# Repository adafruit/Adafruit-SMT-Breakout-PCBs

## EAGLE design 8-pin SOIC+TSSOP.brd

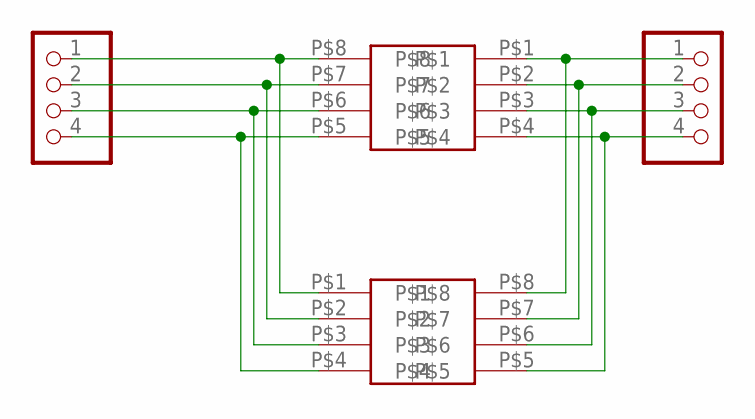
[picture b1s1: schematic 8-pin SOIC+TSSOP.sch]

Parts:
CN1, CN2: PADS-4
U$1: 8-PINSOIC-NW; SO8NW
U$2: 8-PINTSSOP; TSSOP8

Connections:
unnamed: CN1.1, U$1.P$8, U$2.P$1
unnamed: CN2.1, U$1.P$1, U$2.P$8
unnamed: CN2.2, U$1.P$2, U$2.P$7
unnamed: CN2.3, U$1.P$3, U$2.P$6
unnamed: CN2.4, U$1.P$4, U$2.P$5
unnamed: CN1.2, U$1.P$7, U$2.P$2
unnamed: CN1.3, U$1.P$6, U$2.P$3
unnamed: CN1.4, U$1.P$5, U$2.P$4

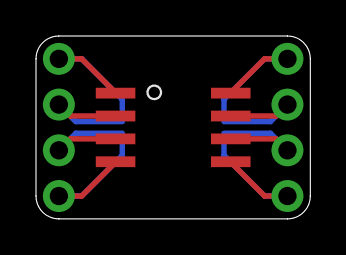
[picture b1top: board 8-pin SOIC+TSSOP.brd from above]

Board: 2 copper layers, 15.2 x 10.2 mm, 4 parts (1 on the bottom side), 8 nets.

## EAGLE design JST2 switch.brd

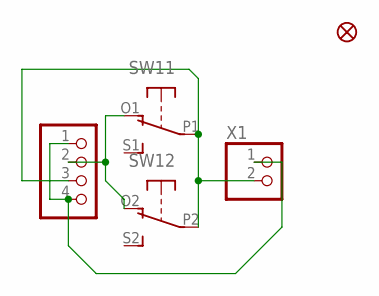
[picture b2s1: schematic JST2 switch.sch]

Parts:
FID1: FIDUCIAL""; FIDUCIAL_1MM
JP1: PADS-4
SW1: DPDT-EG1390; EG1390
X1: CON_JST_PH_2PIN; JSTPH2

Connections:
GND: JP1.1, JP1.4, X1.1
unnamed: JP1.3, SW1.P1, SW1.P2, X1.2
unnamed: JP1.2, SW1.O1 (O), SW1.O2 (O)

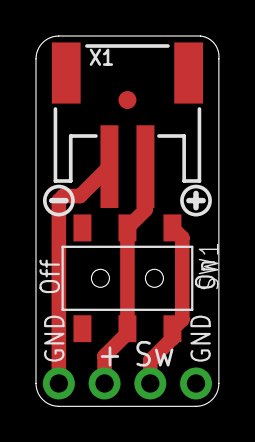
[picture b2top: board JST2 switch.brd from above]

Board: 2 copper layers, 10.2 x 20.6 mm, 7 parts (1 on the bottom side), 3 nets.

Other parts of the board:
U$1: SYMBOL_PLUS
U$2: SYMBOL_MINUS
U$3: ADAFRUIT_5MM

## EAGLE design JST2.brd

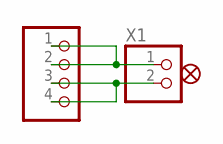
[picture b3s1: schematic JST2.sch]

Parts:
FID1: FIDUCIAL""; FIDUCIAL_1MM
JP1: PADS-4
X1: CON_JST_PH_2PIN; JSTPH2

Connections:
unnamed: JP1.1, JP1.2, X1.1
unnamed: JP1.3, JP1.4, X1.2

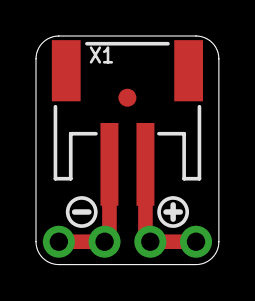
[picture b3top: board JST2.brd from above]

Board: 2 copper layers, 10.2 x 12.7 mm, 6 parts (1 on the bottom side), 2 nets.

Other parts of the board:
U$1: SYMBOL_PLUS
U$2: SYMBOL_MINUS
U$4: ADAFRUIT_3.5MM

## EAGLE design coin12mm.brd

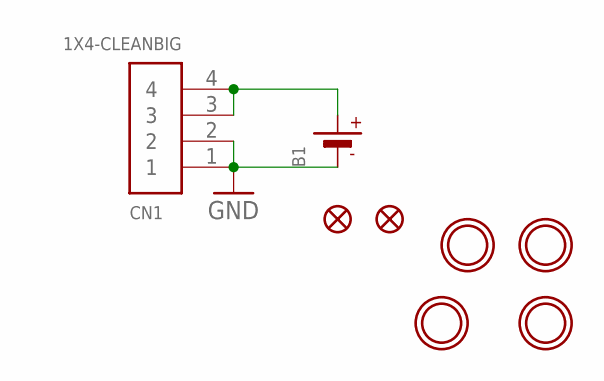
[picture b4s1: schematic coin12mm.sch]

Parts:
B1: BATTERYCR1220_SMT; CR1220
CN1: 1X4-CLEANBIG; 1X04-CLEANBIG
FID1, FID2: FIDUCIAL""; FIDUCIAL_1MM
U$1, U$2, U$3, U$5: MOUNTINGHOLE2.5; MOUNTINGHOLE_2.5_PLATED

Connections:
GND: B1.-, CN1.1, CN1.2
unnamed: B1.+$1 (+), CN1.3, CN1.4

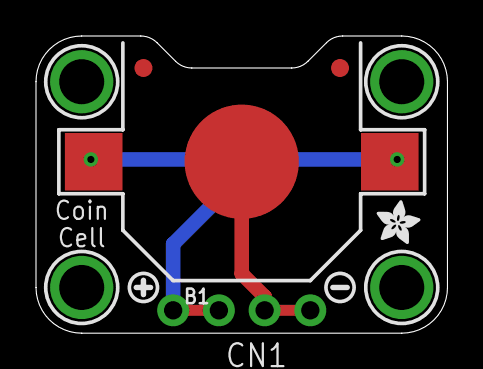
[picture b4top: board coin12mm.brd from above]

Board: 2 copper layers, 22.9 x 16.5 mm, 12 parts (1 on the bottom side), 2 nets.

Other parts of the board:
U$4: ADAFRUIT_5MM
U$6: SYMBOL_PLUS
U$7: SYMBOL_MINUS
U$8: ADAFRUIT_2.5MM

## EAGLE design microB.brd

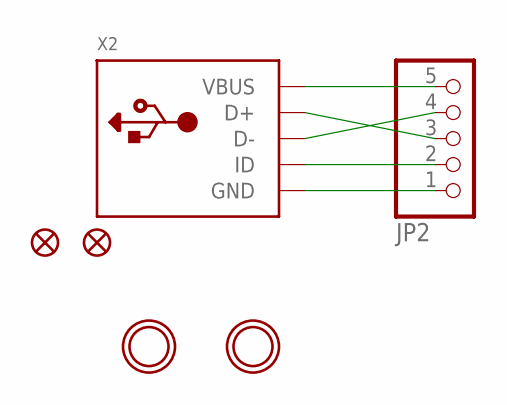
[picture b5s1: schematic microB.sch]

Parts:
FID1, FID2: FIDUCIAL""; FIDUCIAL_1MM
JP2: HEADER-1X570MIL; 1X05_ROUND_70
U$1, U$2: MOUNTINGHOLE2.5; MOUNTINGHOLE_2.5_PLATED
X2: USBMICRO_20329; 4UCONN_20329

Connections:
D+: JP2.3, X2.D+
D-: JP2.4, X2.D-
GND: JP2.1, X2.BASE@1 (GND), X2.BASE@2 (GND), X2.GND, X2.SPRT@1 (GND), X2.SPRT@2 (GND), X2.SPRT@3 (GND), X2.SPRT@4 (GND)
ID: JP2.2, X2.ID
VBUS: JP2.5, X2.VBUS

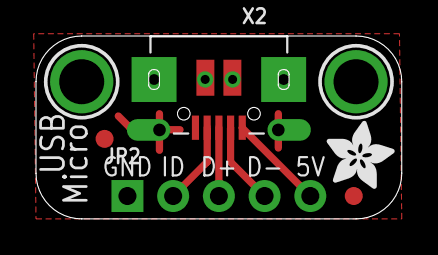
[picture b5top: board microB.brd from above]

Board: 2 copper layers, 20.3 x 10.2 mm, 7 parts (0 on the bottom side), 5 nets.

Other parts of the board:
U$4: ADAFRUIT_3.5MM

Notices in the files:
parts and their libraries:
microbuilder: This work is placed in the public domain, and may be freely used for commercial and non-commercial work with the following conditions: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
